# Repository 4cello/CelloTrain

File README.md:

# CelloTrain
Collection of things I built related to model trains

[Train Presence Detection](presence_detection/README.md)

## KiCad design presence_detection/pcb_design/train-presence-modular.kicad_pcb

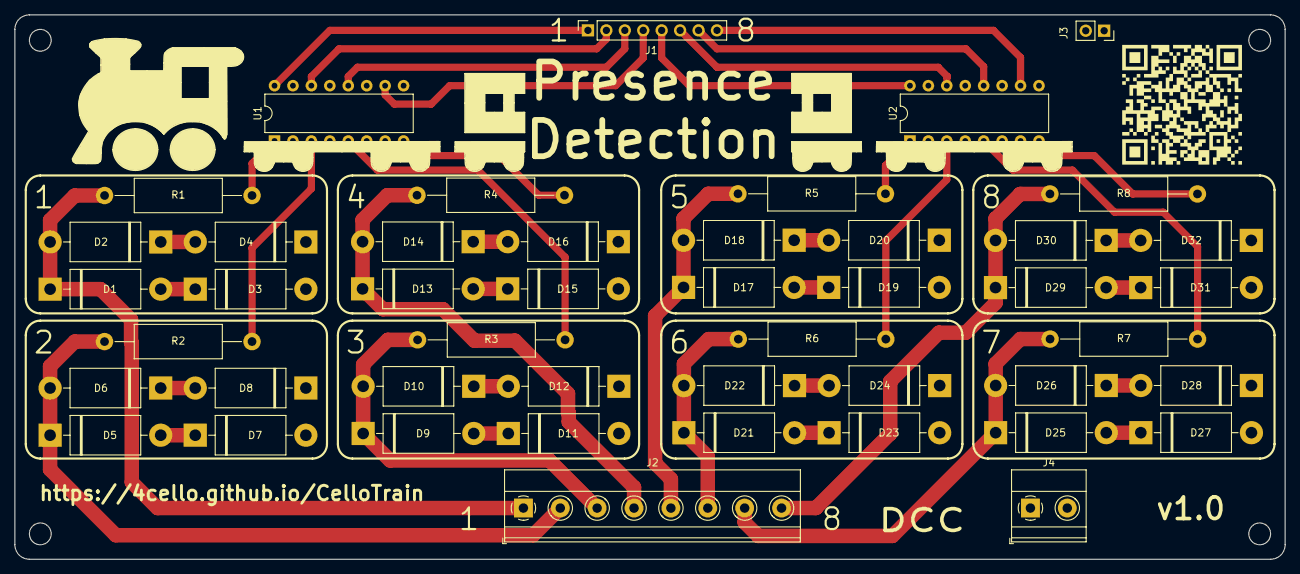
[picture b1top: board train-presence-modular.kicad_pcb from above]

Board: 2 copper layers, 175.0 x 75.0 mm, 47 parts (0 on the bottom side), 42 nets.

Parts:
D1, D2, D3, D4, D5, D6, D7, D8, D9, D10, D11, D12, D13, D14, D15, D16, D17, D18, D19, D20, D21, D22, D23, D24, D25, D26, D27, D28, D29, D30, D31, D32: 1N5401; D_DO-201AD_P15.24mm_Horizontal
J1: Conn_01x08_Female; PinSocket_1x08_P2.54mm_Vertical
J2: Screw_Terminal_01x08; TerminalBlock_Phoenix_MKDS-1,5-8-5.08_1x08_P5.08mm_Horizont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
J3: Conn_01x02_Female; PinSocket_1x02_P2.54mm_Vertical
J4: Screw_Terminal_01x02; TerminalBlock_Phoenix_MKDS-1,5-2-5.08_1x02_P5.08mm_Horizont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
QR*****: QR_CelloTrain
R1, R2, R3, R4, R5, R6, R7, R8: R; R_Axial_DIN0414_L11.9mm_D4.5mm_P20.32mm_Horizontal
U1, U2: LTV-844; DIP-16_W7.62mm

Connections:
/Quad_Sniffer1/Presence1: J1.1, U1.16
/Quad_Sniffer1/Presence2: J1.2, U1.14
/Quad_Sniffer1/Presence3: J1.3, U1.12
/Quad_Sniffer1/Presence4: J1.4, U1.10
/Quad_Sniffer1/Sniffer1/Coupler: R1.2, U1.1
/Quad_Sniffer1/Sniffer2/Coupler: R2.2, U1.3
/Quad_Sniffer1/Sniffer3/Coupler: R3.2, U1.5
/Quad_Sniffer1/Sniffer4/Coupler: R4.2, U1.7
/Quad_Sniffer1/Track1: D1.1, D2.2, J2.1, R1.1
/Quad_Sniffer1/Track2: D5.1, D6.2, J2.2, R2.1
/Quad_Sniffer1/Track3: D9.1, D10.2, J2.3, R3.1
/Quad_Sniffer1/Track4: D13.1, D14.2, J2.4, R4.1
/sheet60A16D49/Presence1: J1.5, U2.16
/sheet60A16D49/Presence2: J1.6, U2.14
/sheet60A16D49/Presence3: J1.7, U2.12
/sheet60A16D49/Presence4: J1.8, U2.10
/sheet60A16D49/Sniffer1/Coupler: R5.2, U2.1
/sheet60A16D49/Sniffer2/Coupler: R6.2, U2.3
/sheet60A16D49/Sniffer3/Coupler: R7.2, U2.5
/sheet60A16D49/Sniffer4/Coupler: R8.2, U2.7
/sheet60A16D49/Track1: D17.1, D18.2, J2.5, R5.1
/sheet60A16D49/Track2: D21.1, D22.2, J2.6, R6.1
/sheet60A16D49/Track3: D25.1, D26.2, J2.7, R7.1
/sheet60A16D49/Track4: D29.1, D30.2, J2.8, R8.1
Booster: D3.2, D4.1, D7.2, D8.1, D11.2, D12.1, D15.2, D16.1, D19.2, D20.1, D23.2, D24.1, D27.2, D28.1, D31.2, D32.1, J4.1, J4.2, U1.2, U1.4, U1.6, U1.8, U2.2, U2.4, U2.6, U2.8
LogicReference: J3.1, J3.2, U1.9, U1.11, U1.13, U1.15, U2.9, U2.11, U2.13, U2.15
unnamed: D1.2, D3.1
unnamed: D2.1, D4.2
unnamed: D5.2, D7.1
unnamed: D6.1, D8.2
unnamed: D10.1, D12.2
unnamed: D9.2, D11.1
unnamed: D13.2, D15.1
unnamed: D14.1, D16.2
unnamed: D17.2, D19.1
unnamed: D18.1, D20.2
unnamed: D21.2, D23.1
unnamed: D22.1, D24.2
unnamed: D25.2, D27.1
unnamed: D26.1, D28.2
unnamed: D29.2, D31.1
unnamed: D30.1, D32.2

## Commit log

2021-05-13 Added Train Presence PCB
2021-05-26 Create presence readme
2021-05-26 Set theme jekyll-theme-cayman
2021-05-26 reworked pages
2021-05-26 added documentation, resized schematics
2021-05-26 moar doc
2021-05-27 updated download links for release
2021-05-27 Fixed Download table?
2021-05-27 added header for TOC
2021-05-27 next attempt at fixing the table
2021-05-27 Killed the table. You won.
2021-05-27 Added an actual landing page
2021-05-27 added Raspberry MCU disclaimer
2021-05-27 Removed title from index, since it's redundant
2022-09-29 WiThrottle2MQTT
2022-09-29 improved withrottle
